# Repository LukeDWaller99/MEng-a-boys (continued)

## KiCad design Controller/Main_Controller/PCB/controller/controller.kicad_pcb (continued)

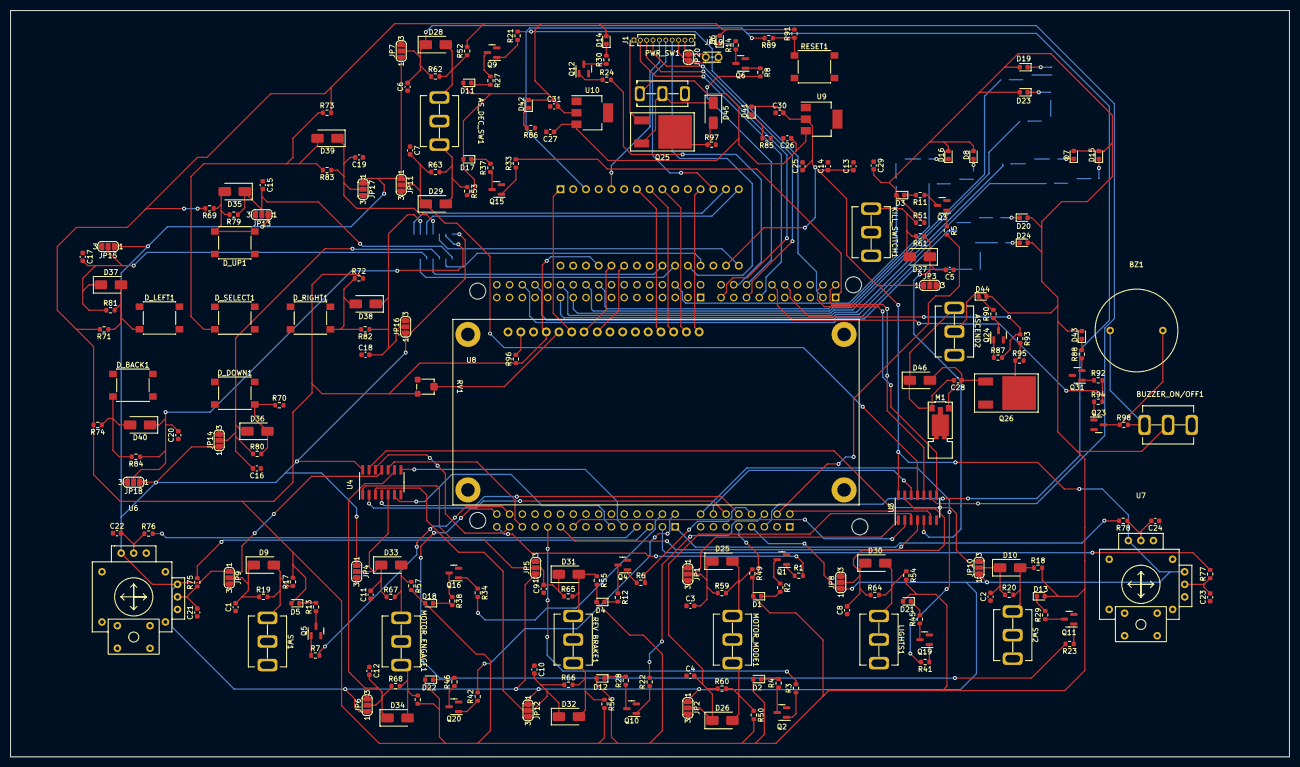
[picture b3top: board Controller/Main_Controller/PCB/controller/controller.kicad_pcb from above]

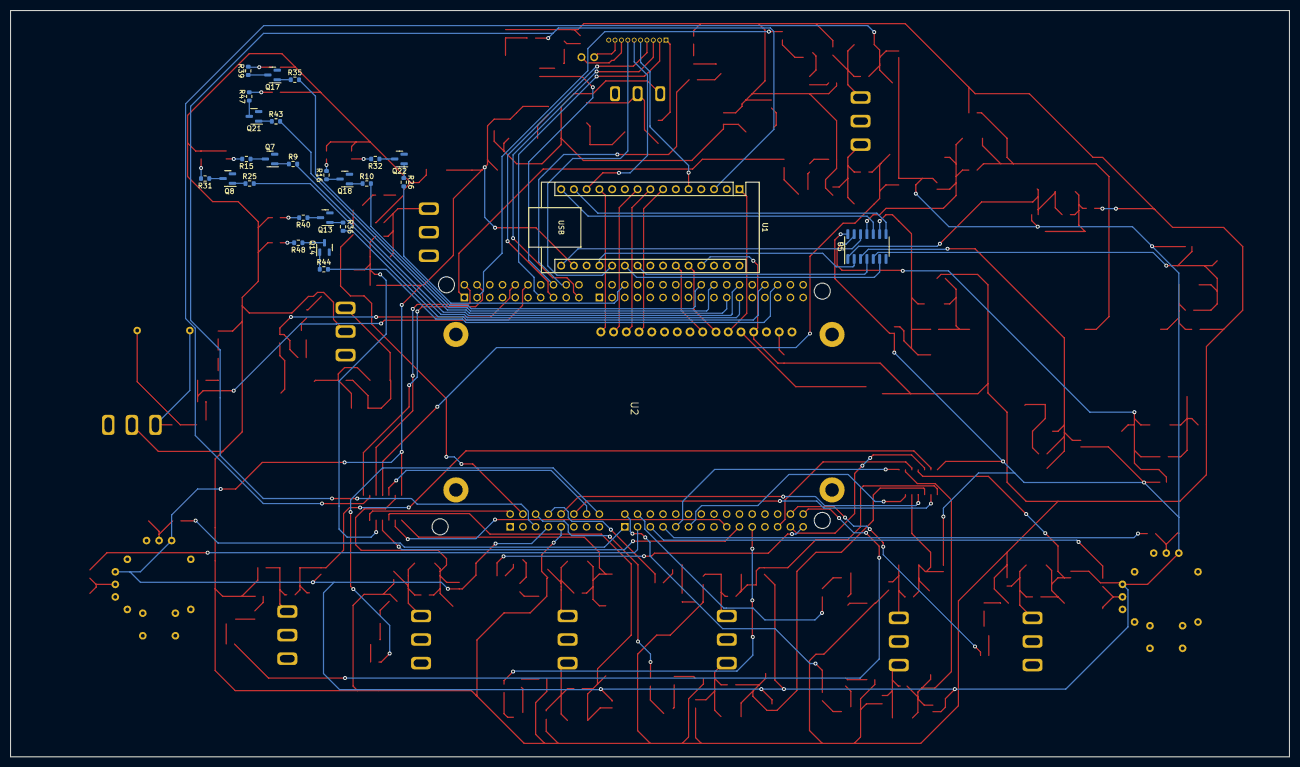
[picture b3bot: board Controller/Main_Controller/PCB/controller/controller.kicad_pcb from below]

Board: 2 copper layers, 255.0 x 148.8 mm, 254 parts (27 on the bottom side), 192 nets.

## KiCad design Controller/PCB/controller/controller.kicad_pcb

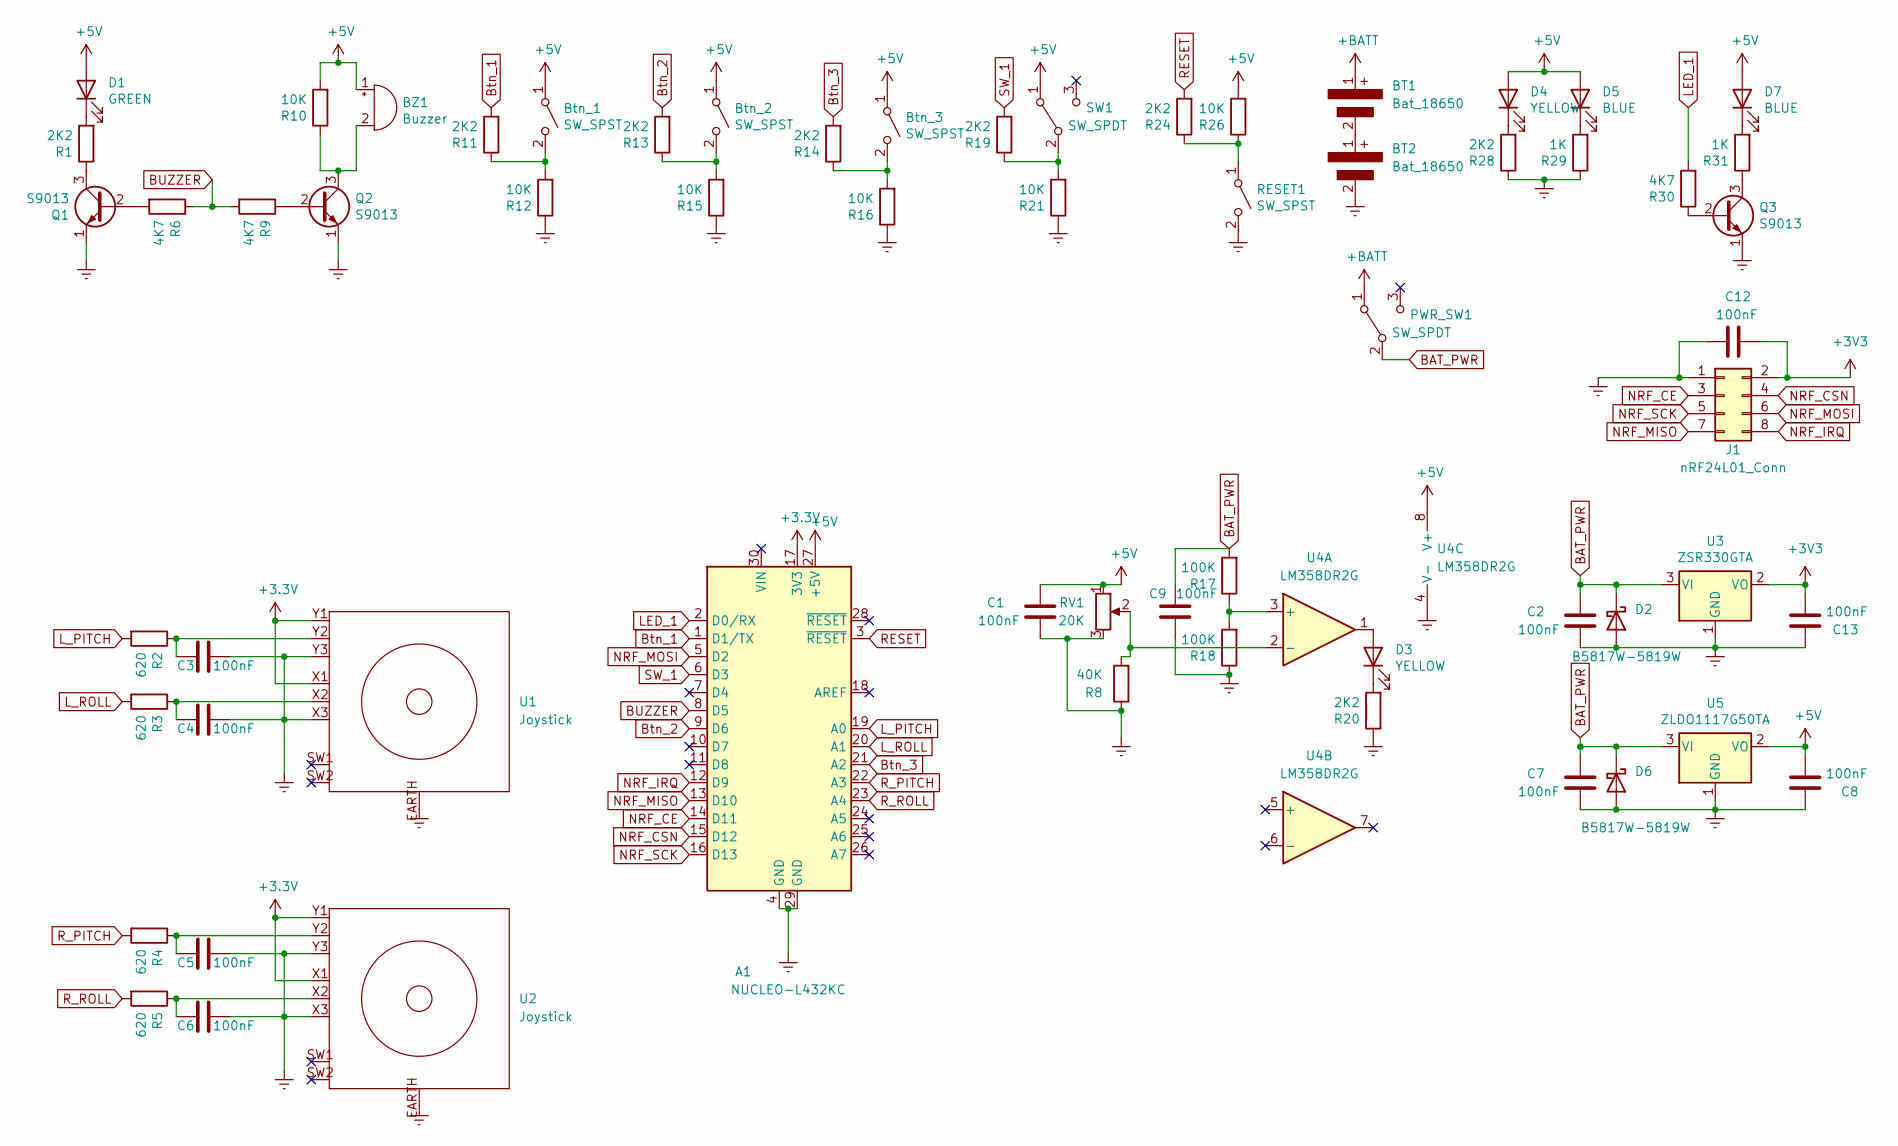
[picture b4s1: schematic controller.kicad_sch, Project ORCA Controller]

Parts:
A1: NUCLEO-L432KC; NUCELO-L432KC_SMD
BT1, BT2: Bat_18650; 18650_Holder(1)
BZ1: Buzzer
Btn_1, Btn_2, Btn_3: SW_SPST; SW_Push_1P1T_NO_6x6mm_H9.5mm
C1, C2, C3, C4, C5, C6, C7, C8, C9, C12, C13: 100nF; C_0603_1608Metric
D1: GREEN; LED_0603_1608Metric
D2, D6: B5817W-5819W; D_SOD-123
D3, D4: YELLOW; LED_0603_1608Metric
D5, D7: BLUE; LED_0603_1608Metric
J1: nRF24L01_Conn; PinHeader_2x04_P2.54mm_Vertical_SMD
PWR_SW1: SW_SPDT; KNX-1-D1
Q1, Q2, Q3: S9013; SOT-23
R1, R11, R13, R14, R19, R20, R24, R28: 2K2; R_0603_1608Metric
R2, R3, R4, R5: 620; R_0603_1608Metric
R6, R9, R30: 4K7; R_0603_1608Metric
R8: 40K; R_0603_1608Metric
R10, R12, R15, R16, R21, R26: 10K; R_0603_1608Metric
R17, R18: 100K; R_0603_1608Metric
R29, R31: 1K; R_0603_1608Metric
RESET1: SW_SPST; SW_Push_1P1T_NO_6x6mm_H9.5mm
RV1: 20K; Variable_Resistor
SW1: SW_SPDT; KNX-1-D1
U1, U2: Joystick
U3: ZSR330GTA; SOT-223
U4: LM358DR2G; SOP-8_3.76x4.96mm_P1.27mm
U5: ZLDO1117G50TA; SOT-223

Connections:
+5V: A1.27 (+5V), BZ1.1 (-), Btn_1.1 (A), Btn_2.1 (A), Btn_3.1 (A), C1.1, C8.2, D1.2 (A), D4.2 (A), D5.2 (A), D7.2 (A), R10.2, R26.2, RV1.1, SW1.1 (A), U4.8 (V+), U5.2 (VO)
+BATT: BT1.1, PWR_SW1.1 (A)
BAT_PWR: C2.1, C7.1, C9.1, D2.1 (K), D6.1 (K), PWR_SW1.2 (B), R17.2, U3.3 (VI), U5.3 (VI)
BUZZER: A1.8 (D5), R6.1, R9.2
Btn_1: A1.1 (D1/TX), R11.2
Btn_2: A1.9 (D6), R13.2
Btn_3: A1.21 (A2), R14.2
Earth: A1.4 (GND), A1.29 (GND), BT2.2, C1.2, C2.2, C3.1, C4.1, C5.1, C6.1, C7.2, C8.1, C9.2, C12.2, C13.1, D2.2 (A), D6.2 (A), J1.1, Q1.1 (E), Q2.1 (E), Q3.1 (E), R8.1, R12.1, R15.1, R16.1, R18.1, R20.1, R21.1, R28.1, R29.1, RESET1.2 (B), RV1.3, U1.EARTH, U1.X3, U1.Y3, U2.EARTH, U2.X3, U2.Y3, U3.1 (GND), U4.4 (V-), U5.1 (GND)
LED_1: A1.2 (D0/RX), R30.2
L_PITCH: A1.19 (A0), R2.2
L_ROLL: A1.20 (A1), R3.2
NRF_CE: A1.14 (D11), J1.3
NRF_CSN: A1.15 (D12), J1.4
NRF_IRQ: A1.12 (D9), J1.8
NRF_MISO: A1.13 (D10), J1.7
NRF_MOSI: A1.5 (D2), J1.6
NRF_SCK: A1.16 (D13), J1.5
unnamed: BT1.2, BT2.1
unnamed: BZ1.2 (+), Q2.3 (C), R10.1
unnamed: Btn_1.2 (B), R11.1, R12.2
unnamed: Btn_2.2 (B), R13.1, R15.2
unnamed: Btn_3.2 (B), R14.1, R16.2
unnamed: C3.2, R2.1, U1.Y2
unnamed: C4.2, R3.1, U1.X2
unnamed: C5.2, R4.1, U2.Y2
unnamed: C6.2, R5.1, U2.X2
unnamed: D1.1 (K), R1.2
unnamed: D3.1 (K), R20.2
unnamed: D3.2 (A), U4.1
unnamed: D4.1 (K), R28.2
unnamed: D5.1 (K), R29.2
unnamed: D7.1 (K), R31.2
unnamed: Q1.2 (B), R6.2
unnamed: Q1.3 (C), R1.1
unnamed: Q2.2 (B), R9.1
unnamed: Q3.2 (B), R30.1
unnamed: Q3.3 (C), R31.1
unnamed: R8.2, RV1.2, U4.2 (-)
unnamed: R17.1, R18.2, U4.3 (+)
unnamed: R19.1, R21.2, SW1.2 (B)
unnamed: R24.1, R26.1, RESET1.1 (A)
RESET: A1.3 (~RESET), R24.2
R_PITCH: A1.22 (A3), R4.2
R_ROLL: A1.23 (A4), R5.2
SW_1: A1.6 (D3), R19.2

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
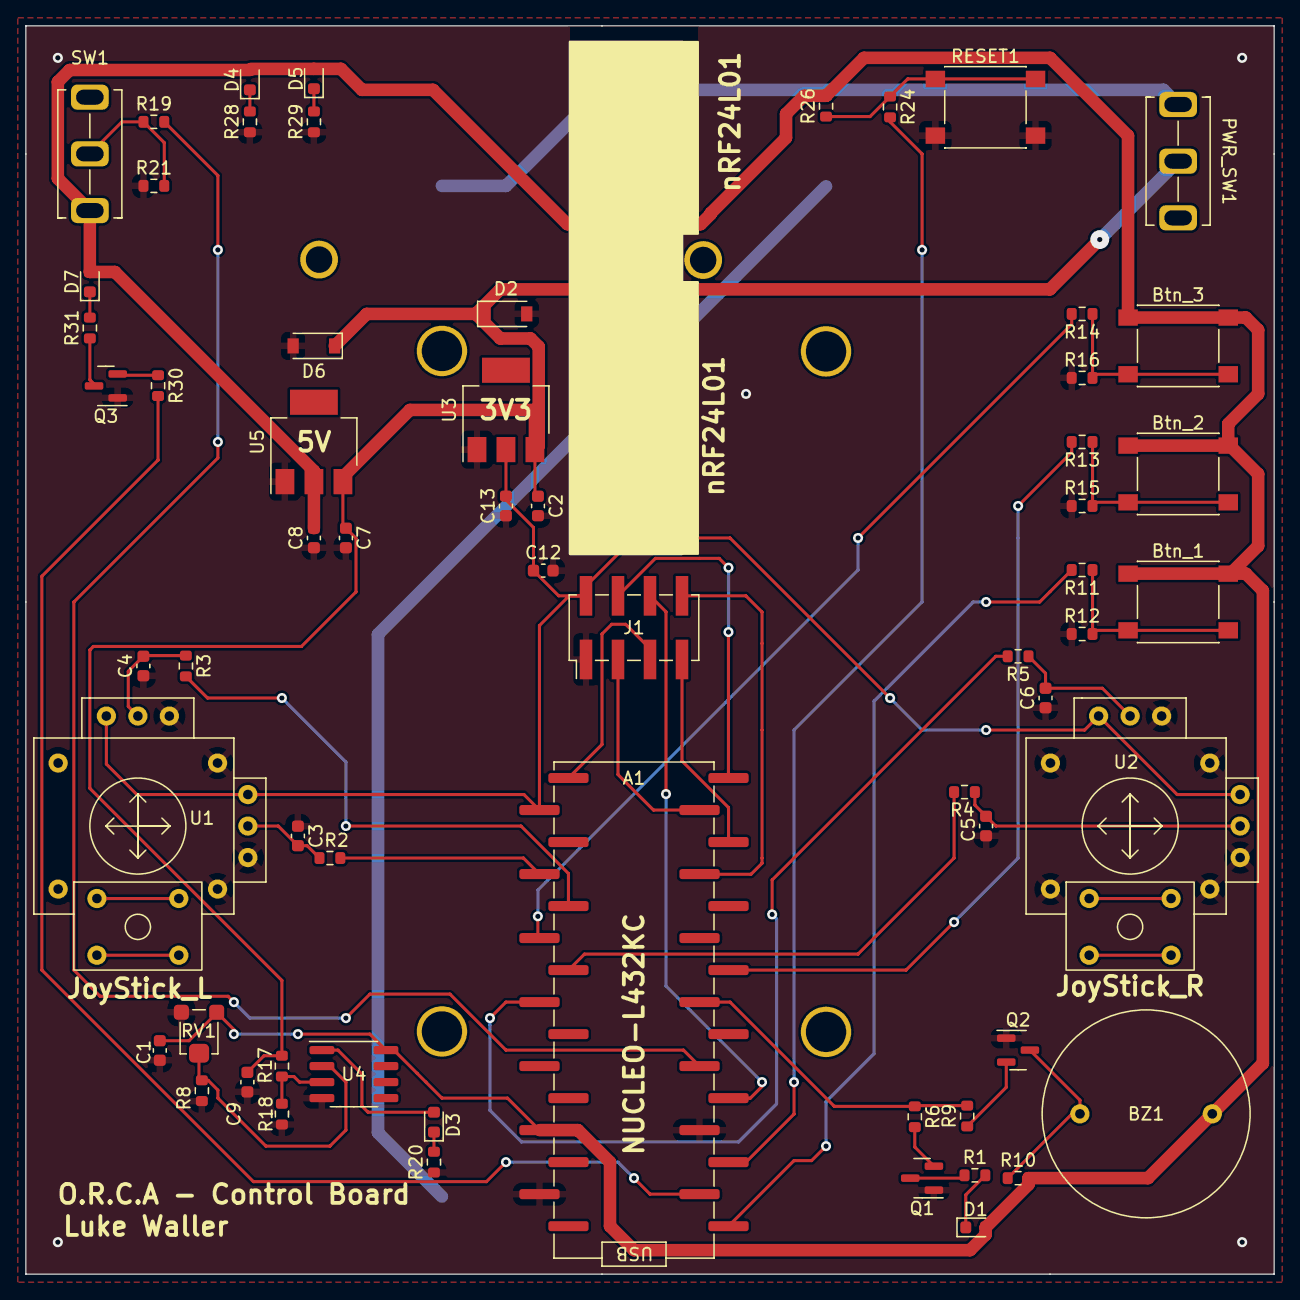
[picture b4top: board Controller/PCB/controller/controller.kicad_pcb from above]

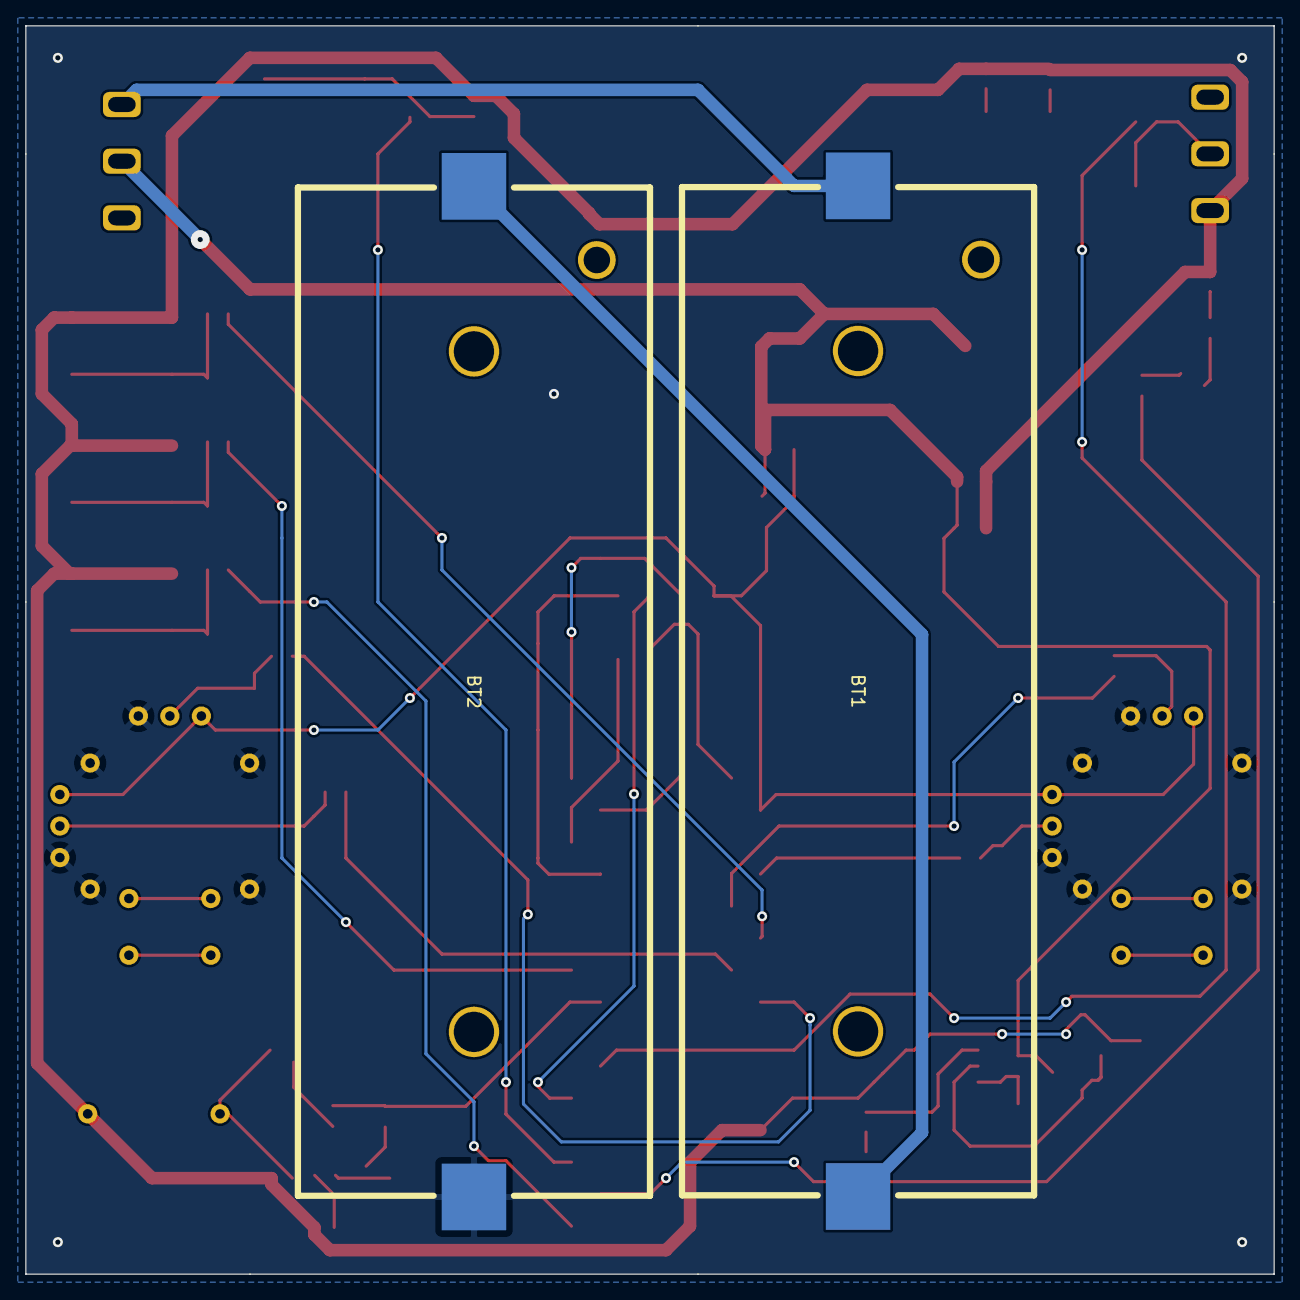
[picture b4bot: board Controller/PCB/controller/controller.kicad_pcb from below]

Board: 2 copper layers, 99.1 x 99.1 mm, 64 parts (2 on the bottom side), 46 nets.

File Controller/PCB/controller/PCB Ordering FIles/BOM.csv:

Comment,Designator,Footprint,JLCPCB Part#
SOT-23,"Q1,Q2,Q3",SOT-23,C6749
GREEN,D1,0603,C72043
B5817W-5819W,"D2,D6",,C8598
YELLOW,"D3,D4",0603,C72038
BLUE,"D5,D7",0603,C72041
39K,R8,0603,C23153
2K2,"R1,R11,R13,R14,R19,R24,R28,R20",0603,C4190
10K,"R10,R12,R15,R16,R21,R26",0603,C25804
100K,"R17,R18",0603,C25803
620,"R2,R3,R4,R5",0603,C23220
4K7,"R9,R6,R30",0603,C23162
LM358DR2G,U4,SOIC-8,C7950
20K,RV1,35WR100KLFTR,C128550
100nF,"C1,C2,C3,C4,C5,C6,C7,C8,C9,C12,C13",0603,C14663
1K,"R29,R31",0603,C21190

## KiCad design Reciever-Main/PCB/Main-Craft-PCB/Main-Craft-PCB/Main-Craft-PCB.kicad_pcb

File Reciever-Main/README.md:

# Reciever/Main Board Specifications
----
## Requirements
The Main Craft will need to communicate with the controller using bi-directional communication. This will involve serveral design considerations including:
1. [x] Microcontroller
	1. [x] NUCELO-F429ZI
2. [x] Inputs
	1. [x] Sensor for detecting how full the basket is
	2. [x] Battery Level detector 
3. [x] Outputs
	1. [x] 4 BLDC Motors for locomotion
	2. [x] 2 H-Bridges for conveyer belt
4. [x] Power
	1. [x] Power Indicator LEDs
	2. [x] Battery Powered
		1. [x] Li-Ion battery
		2. [x] Battery Charger
	3. [x] Suitable Buck Converter to supply appropriate voltages
	4. [x] Reverse polarity protection
	5. [x] Low voltage detection chip
	6. [x] ON/OFF power switch
5. [x] Communication with Controller
	1. [x] RF chip (nRF24L01)
6. [x] Body
7. [x] PCB/Electronics
	1. [x] Schematic  
	2. [x] PCB Layout
8. [x] Testing
	1. [x] Testing individual assemblies on a breadboard
	2. [x] Debugging code to test all individual components on the PCB

## Dependancies/Libraries Used
`nRF24L01P.h` Authored by Owen Edwards (c) - Modified by Luke Waller 2022
`ESC.h` Authored by Luke Waller 2022
`Buzzer.h` Authored by Luke Waller 2022 
----
## Contributions
**Luke Waller**

*Authored*

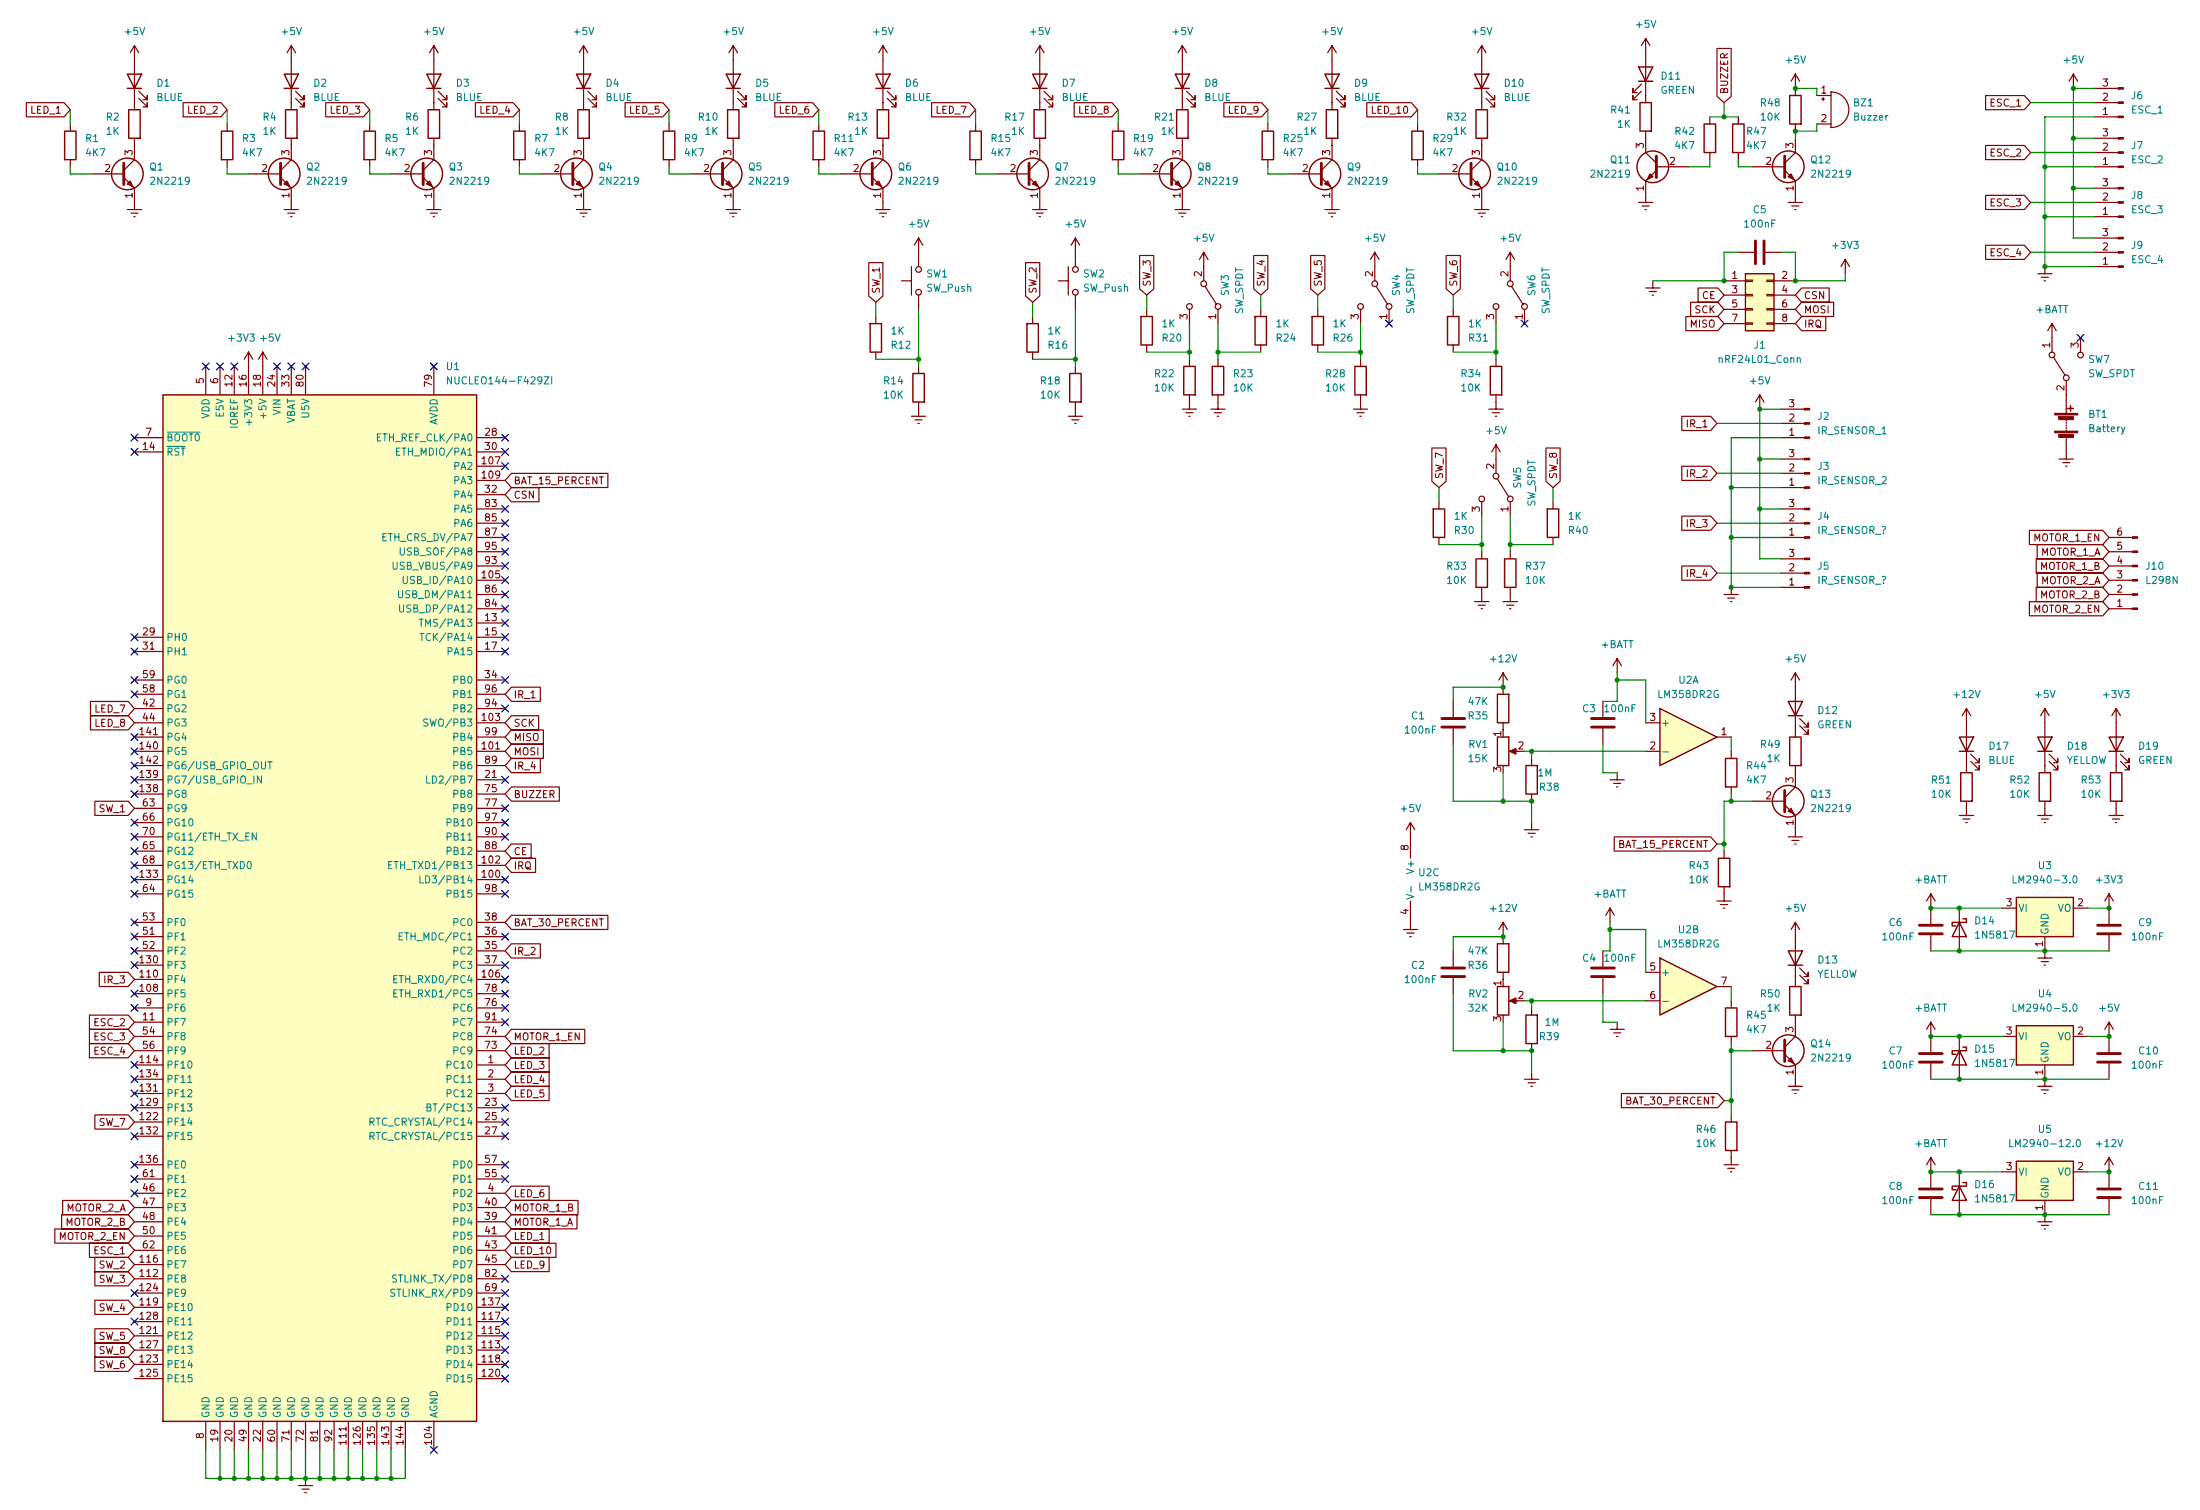
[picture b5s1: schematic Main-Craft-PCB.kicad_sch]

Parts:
BT1: Battery; PinHeader_1x02_P2.54mm_Vertical
BZ1: Buzzer
C1, C2, C3, C4, C5, C6, C7, C8, C9, C10, C11: 100nF; C_0603_1608Metric
D1, D2, D3, D4, D5, D6, D7, D8, D9, D10, D17: BLUE; D_0603_1608Metric
D11, D12, D19: GREEN; D_0603_1608Metric
D13, D18: YELLOW; D_0603_1608Metric
D14, D15, D16: 1N5817; SOD-123
J1: nRF24L01_Conn; PinHeader_2x04_P2.54mm_Vertical_SMD
J2: IR_SENSOR_1; PinHeader_1x03_P2.54mm_Vertical
J3: IR_SENSOR_2; PinHeader_1x03_P2.54mm_Vertical
J4, J5: IR_SENSOR_?; PinHeader_1x03_P2.54mm_Vertical
J6: ESC_1; PinHeader_1x03_P2.54mm_Vertical
J7: ESC_2; PinHeader_1x03_P2.54mm_Vertical
J8: ESC_3; PinHeader_1x03_P2.54mm_Vertical
J9: ESC_4; PinHeader_1x03_P2.54mm_Vertical
J10: L298N; PinHeader_1x06_P2.54mm_Vertical
Q1, Q2, Q3, Q4, Q5, Q6, Q7, Q8, Q9, Q10, Q11, Q12, Q13, Q14: 2N2219; SOT-23
R1, R3, R5, R7, R9, R11, R15, R19, R25, R29, R42, R44, R45, R47: 4K7; R_0603_1608Metric
R2, R4, R6, R8, R10, R12, R13, R16, R17, R20, R21, R24, R26, R27, R30, R31, R32, R40, R41, R49, R50: 1K; R_0603_1608Metric
R14, R18, R22, R23, R28, R33, R34, R37, R43, R46, R48, R51, R52, R53: 10K; R_0603_1608Metric
R35, R36: 47K; R_0603_1608Metric
R38, R39: 1M; R_0603_1608Metric
RV1: 15K; Variable_Resistor
RV2: 32K; Variable_Resistor
SW1, SW2: SW_Push; SW_Push_1P1T_NO_6x6mm_H9.5mm
SW3, SW4, SW5, SW6: SW_SPDT; JS202011SCQN
SW7: SW_SPDT; KNX-1-D1
U1: NUCLEO144-F429ZI; MODULE_NUCLEO-F429ZI_JUST_PINS
U2: LM358DR2G
U3: LM2940-3.0; SOT-223
U4: LM2940-5.0; SOT-223
U5: LM2940-12.0; SOT-223

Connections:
+3V3: C5.2, C9.2, D19.2 (A), J1.2, U1.16 (+3V3), U3.2 (VO)
+5V: BZ1.1 (-), C10.2, D1.2 (A), D2.2 (A), D3.2 (A), D4.2 (A), D5.2 (A), D6.2 (A), D7.2 (A), D8.2 (A), D9.2 (A), D10.2 (A), D11.2 (A), D12.2 (A), D13.2 (A), D18.2 (A), J2.3, J3.3, J4.3, J5.3, J6.3, J7.3, J8.3, J9.3, R48.1, SW1.2, SW2.2, SW3.2 (B), SW4.2 (B), SW5.2 (B), SW6.2 (B), U1.18 (+5V), U2.8 (V+), U4.2 (VO)
+12V: C1.1, C2.1, C11.2, D17.2 (A), R35.2, R36.2, U5.2 (VO)
+BATT: C3.1, C4.1, C6.2, C7.2, C8.2, D14.1 (K), D15.1 (K), D16.1 (K), SW7.1 (A), U2.3 (+), U2.5 (+), U3.3 (VI), U4.3 (VI), U5.3 (VI)
BAT_15_PERCENT: Q13.2 (B), R43.1, R44.2, U1.109 (PA3)
BAT_30_PERCENT: Q14.2 (B), R45.2, R46.1, U1.38 (PC0)
BUZZER: R42.1, R47.1, U1.75 (PB8)
CE: J1.3, U1.88 (PB12)
CSN: J1.4, U1.32 (PA4)
ESC_1: J6.2, U1.62 (PE6)
ESC_2: J7.2, U1.11 (PF7)
ESC_3: J8.2, U1.54 (PF8)
ESC_4: J9.2, U1.56 (PF9)
Earth: BT1.2 (-), C1.2, C2.2, C3.2, C4.2, C5.1, C6.1, C7.1, C8.1, C9.1, C10.1, C11.1, D14.2 (A), D15.2 (A), D16.2 (A), J1.1, J2.1, J3.1, J4.1, J5.1, J6.1, J7.1, J8.1, J9.1, Q1.1 (E), Q2.1 (E), Q3.1 (E), Q4.1 (E), Q5.1 (E), Q6.1 (E), Q7.1 (E), Q8.1 (E), Q9.1 (E), Q10.1 (E), Q11.1 (E), Q12.1 (E), Q13.1 (E), Q14.1 (E), R14.2, R18.2, R22.2, R23.2, R28.2, R33.2, R34.2, R37.2, R38.1, R39.1, R43.2, R46.2, R51.2, R52.2, R53.2, RV1.3, RV2.3, U1.8 (GND), U1.19 (GND), U1.20 (GND), U1.22 (GND), U1.49 (GND), U1.60 (GND), U1.71 (GND), U1.72 (GND), U1.81 (GND), U1.92 (GND), U1.111 (GND), U1.126 (GND), U1.135 (GND), U1.143 (GND), U1.144 (GND), U2.4 (V-), U3.1 (GND), U4.1 (GND), U5.1 (GND)
IRQ: J1.8, U1.102 (ETH_TXD1/PB13)
IR_1: J2.2, U1.96 (PB1)
IR_2: J3.2, U1.35 (PC2)
IR_3: J4.2, U1.110 (PF4)
IR_4: J5.2, U1.89 (PB6)
LED_1: R1.1, U1.41 (PD5)
LED_2: R3.1, U1.73 (PC9)
LED_3: R5.1, U1.1 (PC10)
LED_4: R7.1, U1.2 (PC11)
LED_5: R9.1, U1.3 (PC12)
LED_6: R11.1, U1.4 (PD2)
LED_7: R15.1, U1.42 (PG2)
LED_8: R19.1, U1.44 (PG3)
LED_9: R25.1, U1.45 (PD7)
LED_10: R29.1, U1.43 (PD6)
MISO: J1.7, U1.99 (PB4)
MOSI: J1.6, U1.101 (PB5)
MOTOR_1_A: J10.5, U1.39 (PD4)
MOTOR_1_B: J10.4, U1.40 (PD3)
MOTOR_1_EN: J10.6, U1.74 (PC8)
MOTOR_2_A: J10.3, U1.47 (PE3)
MOTOR_2_B: J10.2, U1.48 (PE4)
MOTOR_2_EN: J10.1, U1.50 (PE5)
unnamed: BT1.1 (+), SW7.2 (B)
unnamed: BZ1.2 (+), Q12.3 (C), R48.2
unnamed: D1.1 (K), R2.1
unnamed: D2.1 (K), R4.1
unnamed: D3.1 (K), R6.1
unnamed: D4.1 (K), R8.1
unnamed: D5.1 (K), R10.1
unnamed: D6.1 (K), R13.1
unnamed: D7.1 (K), R17.1
unnamed: D8.1 (K), R21.1
unnamed: D9.1 (K), R27.1
unnamed: D10.1 (K), R32.1
unnamed: D11.1 (K), R41.1
unnamed: D12.1 (K), R49.1
unnamed: D13.1 (K), R50.1
unnamed: D17.1 (K), R51.1
unnamed: D18.1 (K), R52.1
unnamed: D19.1 (K), R53.1
unnamed: Q1.2 (B), R1.2
unnamed: Q1.3 (C), R2.2
unnamed: Q2.2 (B), R3.2
unnamed: Q2.3 (C), R4.2
unnamed: Q3.2 (B), R5.2
unnamed: Q3.3 (C), R6.2
unnamed: Q4.2 (B), R7.2
unnamed: Q4.3 (C), R8.2
unnamed: Q5.2 (B), R9.2
unnamed: Q5.3 (C), R10.2
unnamed: Q6.2 (B), R11.2
unnamed: Q6.3 (C), R13.2
unnamed: Q7.2 (B), R15.2
unnamed: Q7.3 (C), R17.2
unnamed: Q8.2 (B), R19.2
unnamed: Q8.3 (C), R21.2
unnamed: Q9.2 (B), R25.2
unnamed: Q9.3 (C), R27.2
unnamed: Q10.2 (B), R29.2
unnamed: Q10.3 (C), R32.2
unnamed: Q11.2 (B), R42.2
unnamed: Q11.3 (C), R41.2
unnamed: Q12.2 (B), R47.2
unnamed: Q13.3 (C), R49.2
unnamed: Q14.3 (C), R50.2
unnamed: R12.1, R14.1, SW1.1
unnamed: R16.1, R18.1, SW2.1
unnamed: R20.1, R22.1, SW3.3 (C)
unnamed: R23.1, R24.1, SW3.1 (A)
unnamed: R26.1, R28.1, SW4.3 (C)
unnamed: R30.1, R33.1, SW5.3 (C)
unnamed: R31.1, R34.1, SW6.3 (C)
unnamed: R35.1, RV1.1
unnamed: R36.1, RV2.1
unnamed: R37.1, R40.1, SW5.1 (A)
unnamed: R38.2, RV1.2, U2.2 (-)
unnamed: R39.2, RV2.2, U2.6 (-)
unnamed: R44.1, U2.1
unnamed: R45.1, U2.7
SCK: J1.5, U1.103 (SWO/PB3)
SW_1: R12.2, U1.63 (PG9)
SW_2: R16.2, U1.116 (PE7)
SW_3: R20.2, U1.112 (PE8)
SW_4: R24.2, U1.119 (PE10)
SW_5: R26.2, U1.121 (PE12)
SW_6: R31.2, U1.123 (PE14)
SW_7: R30.2, U1.122 (PF14)
SW_8: R40.2, U1.127 (PE13)

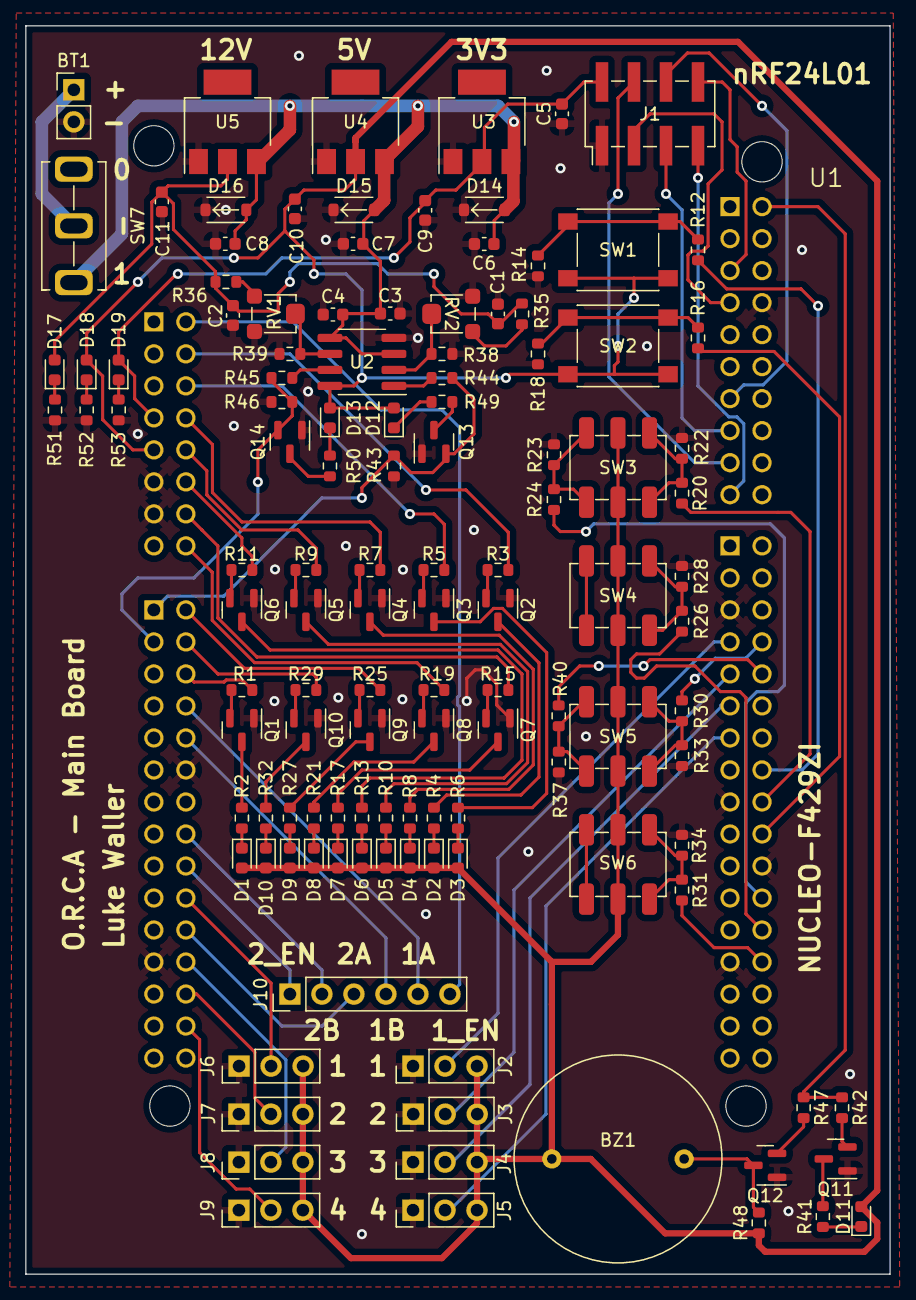
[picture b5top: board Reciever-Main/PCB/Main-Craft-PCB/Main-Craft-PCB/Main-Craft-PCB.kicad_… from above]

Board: 2 copper layers, 68.6 x 99.1 mm, 123 parts (0 on the bottom side), 103 nets.

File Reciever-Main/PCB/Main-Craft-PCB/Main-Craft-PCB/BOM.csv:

Comment,Designator,Footprint,JLCPCB Part#
BLUE,"D1,D2,D3,D4,D5,D6,D7,D8,D9,D10,D17",603,C72041
YELLOW,"D13,D18",603,C72038
GREEN,"D11,D12,D19",603,C72043
SOT-23,"Q1,Q2,Q3,Q4,Q5,Q6,Q7,Q8,Q9,Q10,Q11,Q12,Q13,Q14",SOT-23,C6749
B5817W-5819W,,,C8598
1M,"R38,R39",603,C22935
10K,"R14,R18,R22,R23,R28,R33,R34,R37,R43,R46,R48,R51,R52,R53",603,C25803
4k7,"R1,R3,R5,R7,R9,R11,R19,R25,R29,R42,R44,R45,47",603,C23162
47K,"R35,R36",603,C25819
LM358DR2G,U2,SOP-8,C7950
1K,"R2,R4,R6,R8,R10,R12,R13,R16,R17,R20,R21,R24,R26,R27,30,R31,R32,30,41,R49,50",603,C21190
1N5817M,"D14,D15,D16",SOD-123,C8598
100nF,"C1,C2,C3,C4,C5,C6,C7,C8,C9,C10,C11",603,C14663
50K,"RV1,RV2",VG039NCHXT,C145161

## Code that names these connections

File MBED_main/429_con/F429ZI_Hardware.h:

#ifndef __HARDWARE_H__
#define __HARDWARE_H__
//NUCLEO-F429ZI HARDWARE
#include <mbed.h>

//onboard peripherals
#define USR_BTN PC_13
#define USER_LED_GREEN PB_0
#define USER_LED_BLUE PB_7
#define USER_LED_RED PB_14

//SPI PINS DEFINED ON PCB
// #define CLK_1 PB_3
// #define MISO_1 PB_4
// #define MOSI_1 PB_5

//SPI PINS DEFINED IN EXAMPLES
//#define CS_1 PD_13
#define CLK_2 D13   //PA_5
#define MISO_2 PB_5 //PA_7 or PB_5 - D11
#define MOSI_2 D12 //PA_6


//Comms
#define CLK_1 PB_3
#define MISO_1 PB_4
#define MOSI_1 PB_5
#define CS_1 PD_13

// joystick pins
#define L_PITCH PC_3   
#define L_ROLL  PF_3
#define R_PITCH PC_0
#define R_ROLL  PA_3 

#define PITCH_UPPER_LIMIT  1 
#define PITCH_LOWER_LIMIT  -1
#define ROLL_UPPER_LIMIT   1
#define ROLL_LOWER_LIMIT   -1

#define TRANSFER_SIZE   5
#define MULTIPLYING_FACTOR  2.0f
#define POT_OFFSET          1.0f

#define LEFT_PITCH_FWD  '1','1','0','0','\0'
#define LEFT_ROLL_FWD   '1','2','0','0','\0'
#define RIGHT_PITCH_FWD '1','3','0','0','\0'
#define RIGHT_ROLL_FWD  '1','4','0','0','\0'

#define LEFT_PITCH_REV  '1','1','1','0','\0'
#define LEFT_ROLL_REV   '1','2','1','0','\0'
#define RIGHT_PITCH_REV '1','3','1','0','\0'
#define RIGHT_ROLL_REV  '1','4','1','0','\0'

//SWITCHES
#define ASCEND PB_8 //3
#define DESCEND PB_9 //4
#define MOTOR_MODE_1 PF_2  //5
#define MOTOR_MODE_2 PH_1  //6
#define LIGHTS PG_2 //7
#define MOTOR_EN PF_10 //8
#define MOTOR_DE PF_5 //9
#define BRAKE_MODE PD_2 //10
#define REV_MODE PC_12 //11
#define SWITCH_1 PD_0 //1
#define SWITCH_2 PD_1 //2
#define KILL_SWITCH PC_8

// // input buttons
// #define BTN1    PF_5 // D1
// #define BTN2    PF_10 // D6
// #define BTN3    PF_0 // A2

// General LEDs
#define LED_1 PD_14
#define LED_2 PD_15
#define SWITCH_1_LED PF_9
#define SWITCH_2_LED PG_1
#define MOTOR_MODE_1_LED PG_0
#define MOTOR_MODE_2_LED PH_0
#define LIGHTS_LED PG_3
#define EN_LED PD_6
#define DE_LED PD_7 
#define ASCEND_LED PB_15
#define DESCEND_LED PC_6
#define KILL_LED PC_9
#define REV_LED PC_10
#define BRAKE_LED PC_11

// Buzzer and Vibration Motor
// #define BUZZER  PA_6
// #define VIB_MOTOR PA_5

//Collision LEDs
#define COL_SENSE_1 PE_7
#define COL_SENSE_2 PD_12
#define COL_SENSE_3 PE_10
#define COL_SENSE_4 PD_11
#define COL_SENSE_5 PE_14
#define COL_SENSE_6 PE_15
#define COL_SENSE_7 PE_8
#define COL_SENSE_8 PE_11


#endif

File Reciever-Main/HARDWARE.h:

/**
 * @file HARDWARE.h
 * 
 * @author Luke Waller
 */
#ifndef __HARDWARE_H__
#define __HARDWARE_H__

#include <PinNames.h>

// nRF24L01
#define MOSI    PB_5
#define MISO    PB_4
#define SCK     PB_3
#define CSN     PA_4
#define CE      PB_13
#define IRQ     PB_12

// BLDC motor pins
#define FWD_LHS_MOTOR   PE_6
#define FWD_RHS_MOTOR   PF_7
#define REV_LHS_MOTOR   PF_8
#define REV_RHS_MOTOR   PF_9

// Conveyer Motors
#define CONV_MOTOR_1_A      PD_4
#define CONV_MOTOR_1_B      PD_3
#define CONV_MOTOR_2_A      PE_2
#define CONV_MOTOR_2_B      PE_4
#define CONV_MOTOR_1_ENABLE PC_8
#define CONV_MOTOR_2_ENABLE PE_5

// LEDs
#define LED_1   PD_5
#define LED_2   PC_9
#define LED_3   PC_10
#define LED_4   PC_11
#define LED_5   PC_12
#define LED_6   PD_2
#define LED_7   PG_2
#define LED_8   PG_3
#define LED_9   PD_7
#define LED_10  PD_6

// Inputs
#define BTN_1   PG_9    // SW1 - working
#define BTN_2   PE_7    // SW2 - working
#define SW_1    PE_8    // SW3 - working
#define SW_2    PE_10   // SW4 - working
#define SW_3    PE_12   // SW5 - not in use
#define SW_4    PE_14   // SW6 - not in use 
#define SW_5    PF_14   // SW7 - not in use
#define SW_6    PE_13   // SW8 - not in use

// IR Sensors
#define IR_1    PB_1 // working
#define IR_2    PC_2 // not in use
#define IR_3    PF_4 // not in use
#define IR_4    PB_6 // working

// Buzzer
#define BUZZER  PB_8

// Low Battery Inputs
#define Bat_30_PERCENT PC_0
#define Bat_15_PERCENT PA_3

#endif

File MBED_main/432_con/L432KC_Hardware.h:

#ifndef __L432KC_HARDWARE_H__
#define __L432KC_HARDWARE_H__
//NUCLEO-L432KC HARDWARE

#define L4_USER_LED_GREEN PB_3

// //SPARE
// #define SP_D7 D7
// #define SP_D8 D8
// #define SP_A4 A4
// #define SP_A5 A5

//LCD
#define LCD_RS D1 //PA_9 was a4 d1work
#define LCD_E D0 //PA_7 was a6 d0works
#define LCD_RW A7 //PA_2
#define LCD_D4 D4 //PB_7
#define LCD_D5 D5 //PB_6
#define LCD_D6 D6 //PB_1
#define LCD_D7 D9 //PA_8 was D9

//SPI
#define mosi D2 //PA_12 
#define miso D10 //PA_11
#define SCK  A1 //PA_1
#define CS D3 //PB_0 // mosi, miso, sclk, nSS

//D-PAD BUTTONS
#define D_UP A0 //PA_0
#define D_LEFT A2 //PA_3
#define D_RIGHT D11 //PB_5
#define D_DOWN A3 //PA_4
#define D_SEL D12 //PB_4 same as MISO
#define D_BACK D13 //PB_3 same as SCK

// //SPI Pins - AS IN MANUAL
// #define MOSI PA_12 //D2
// #define MISO PA_11 //D10
// #define SCK PA_1 //A1
// //#define SSEL A3//PA_4/A3 worked but taken

#endif
